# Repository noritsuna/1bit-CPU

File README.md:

# 1bit CPU made with ASIC (ISHI-Kai's OpenMPW PTC06-1)
[naoto64氏の1bit-CPU](https://naoto64.github.io/1bit-CPU/)を[ISHI会版OpenMPW PTC06-1](https://ishi-kai.org/openmpw/shuttle/ptc06/2024/07/06/shuttle_ISHI-Kai_OpenMPW-PTC06-1_start.html)を利用して、ASIC化しました！  
サイズは、280um x 65um くらいとなりました。元の基板が85mm x 70mmですのでおよそ36万分の1に縮小できました！  

# 論理回路化
まずは、74HC series logic IC部分を論理回路に起こし直して、シミュレーションを行いました。  
シミュレーションには[logicsim](http://www.cburch.com/logisim/)を利用しています。  

## 各種回路
本家のサンプル回路をシミュレーションしました。  

-[LED点滅回路](logicsim/LED_brink.circ)
 
-[LED点灯回路](logicsim/LED_flash.circ)
 
-[NOP回路](logicsim/NOP.circ)

# AISC化
ここから、ASICにするための設計を行なっていきます。  

## 回路図
まずは、回路図を書きます。とは言っても、シミュレーション時に回路としては完成しているので、それをxschemで書き直しただけです。  

-[回路図](xschem/1bit-CPU.sch)

## レイアウト
続いて、論理回路のレイアウトをします。  
論理回路は実際には、P-FETやN-FETを組み合わせて機能が実現されています。  

もちろん、P-FETやN-FETを組み合わせて、自分で論理回路のレイアウトをしても良いのですが、通常スタセル（スタンダードセル）という物が用意されています。  
要は、P-FETやN-FETを組み合わせて作られている論理回路ライブラリです。3つ目が拡大図でP-FETとN-FETで構成されているのが確認できるかと思います。  

回路図そのままで、スタセルを配置してみたパターンです。  

### 一列化
このまま配線するだけでも良いのですが、通常のスタセルはVerilogなどから自動的にレイアウトに変換する時に使用するように作成されています。  
そのため、スタセルは自動レイアウトを考慮して、下の図のように縦の長さが固定されて、上部にVDDがあり下部にVSS(GND)があるタイル状の形状をしています。これらを横に並べて利用することで、VSSやVSSが接続されて、自動ルーティングや配置がしやすいように作られています。  

そのため、人間が見やすい回路図の形で配置し、配線すると無駄が多くなります。  
そこで、回路図をこのタイル型レイアウトに合わせて、一列に並ぶように書き換えます。  
（通常は、この手の論理回路で設計するロジック回路を手でレイアウトすることはあまり無いと思いますので、今回は結構特殊なシチュエーションとなります。）  

-[1ライン化回路図](xschem/1bit-CPU_1line.sch)

### 最終レイアウト
一列化して、配線したレイアウトです。  

-[レイアウト](klayout/1bit-CPU.gds)

## LVS
手配線のため回路図とレイアウトが間違っている可能性があるため、LVS（Layout vs Schematic）をかけるのですが、OpenRule1umのスタセルの作りが微妙のため、完全体とはなりませんでした。  
そのため、目LVSで乗り切りました。とは言っても、接続先は下の図（LVSの配線ハイライト）のように強調表示されるためそれほど大変ではありません。  

## パッドへの接続
最後に、実際の半導体上のパッド（ピン）に各ポートを接続します。  
本来ならピンの設定（INやOUT、デジタルかアナログかなどを指定する）があるのですが、そこの設定はNDAの範囲内での設定となるため、ここでは行いません。そのため、これは実質的に仮配線となります。  

-[パッド付きレイアウト](klayout/1bit-CPU_frame.gds)

## WSL Image
上記の回路図やシミュレーション、レイアウト、DRC、LVSを実行するための環境をセットアップしたWSLイメージを用意しています。

- [WSL Image](https://www.noritsuna.jp/download/ubuntu2204_PTC06-1.tar.xz)
    - ID: ishikai
    - Pass: ishikai

### Installing WSL Images
`wsl --import-in-place ubuntu2204_PTC06-1 .\ubuntu2204_PTC06-1\ext4.vhdx`

起動には"ubuntu2204_PTC06-1.lnk"をご利用ください。  

### Deleting WSL Images
イメージも削除されるので注意してください。    

`wsl --unregister ubuntu2204_PTC06-1`

# [本チップ用ボード](kicad/1bit-CPU_board)
メモリや外部クロック、動作確認用のLEDを搭載したボードをKiCADで設計しました。  

[本チップ用ボードディレクトリ：KiCADファイル](kicad/1bit-CPU_board)

## 動作確認
ボードが到着したので、部品を実装して動作確認しました。  
無事に、本家の1bit-CPUボードと同じ動きをしております！  
※クロックが微妙にずれているため、同期はしてません。

[ボード：YouTube動画](https://youtube.com/shorts/-G9ZElhzAAo?feature=share)
[ボード：動画ファイル](images/1bit-CPU_board.mp4)

# [本チップ用ラズパイHAT](kicad/1bit-CPU_HAT)
ラズパイHATをKiCADで設計しました。  
ただ、本CPUは5V動作で、ラズパイは3.3V動作のため、レベル変換が必要となります。  

## インバータの応用
レベル変換の一つの手として、バッファ回路を使う手があります。  
バッファ回路＝インバータ回路*2です。そこで、今回は、みんなで実装したインバータ回路をそのまま使うことにしました。  

### インバータの動作確認
- [インバータ動作チェック用AD3設定ファイル](kicad/1bit-CPU_HAT/Inverter_checker.dwf3work)

## クロック源
クロック源として、りょうすさんが実装したVCOを流用しました。  

### クロック源の動作確認
- [VCO動作チェック用AD3設定ファイル](kicad/1bit-CPU_HAT/VCO_checker.dwf3work)

## HATの実装
チップ内にあるインバータ回路やVCOを利用したため、外部回路は3つのみとなっています。  

- LED点灯用回路
- リセット回路
- VCO用電圧制御回路

- [本チップ用ラズパイHATディレクトリ：KiCADファイル](kicad/1bit-CPU_HAT)

## 実行用インタープリター
ラズパイ用のプログラム実行用のインタープリターの実装です。

- [本CPU用インタープリター](kicad/1bit-CPU_HAT/program/1bit-CPU_interpreter.py)

## 実際のボード
実際にラズパイZEROに装着した状態と動作状態。

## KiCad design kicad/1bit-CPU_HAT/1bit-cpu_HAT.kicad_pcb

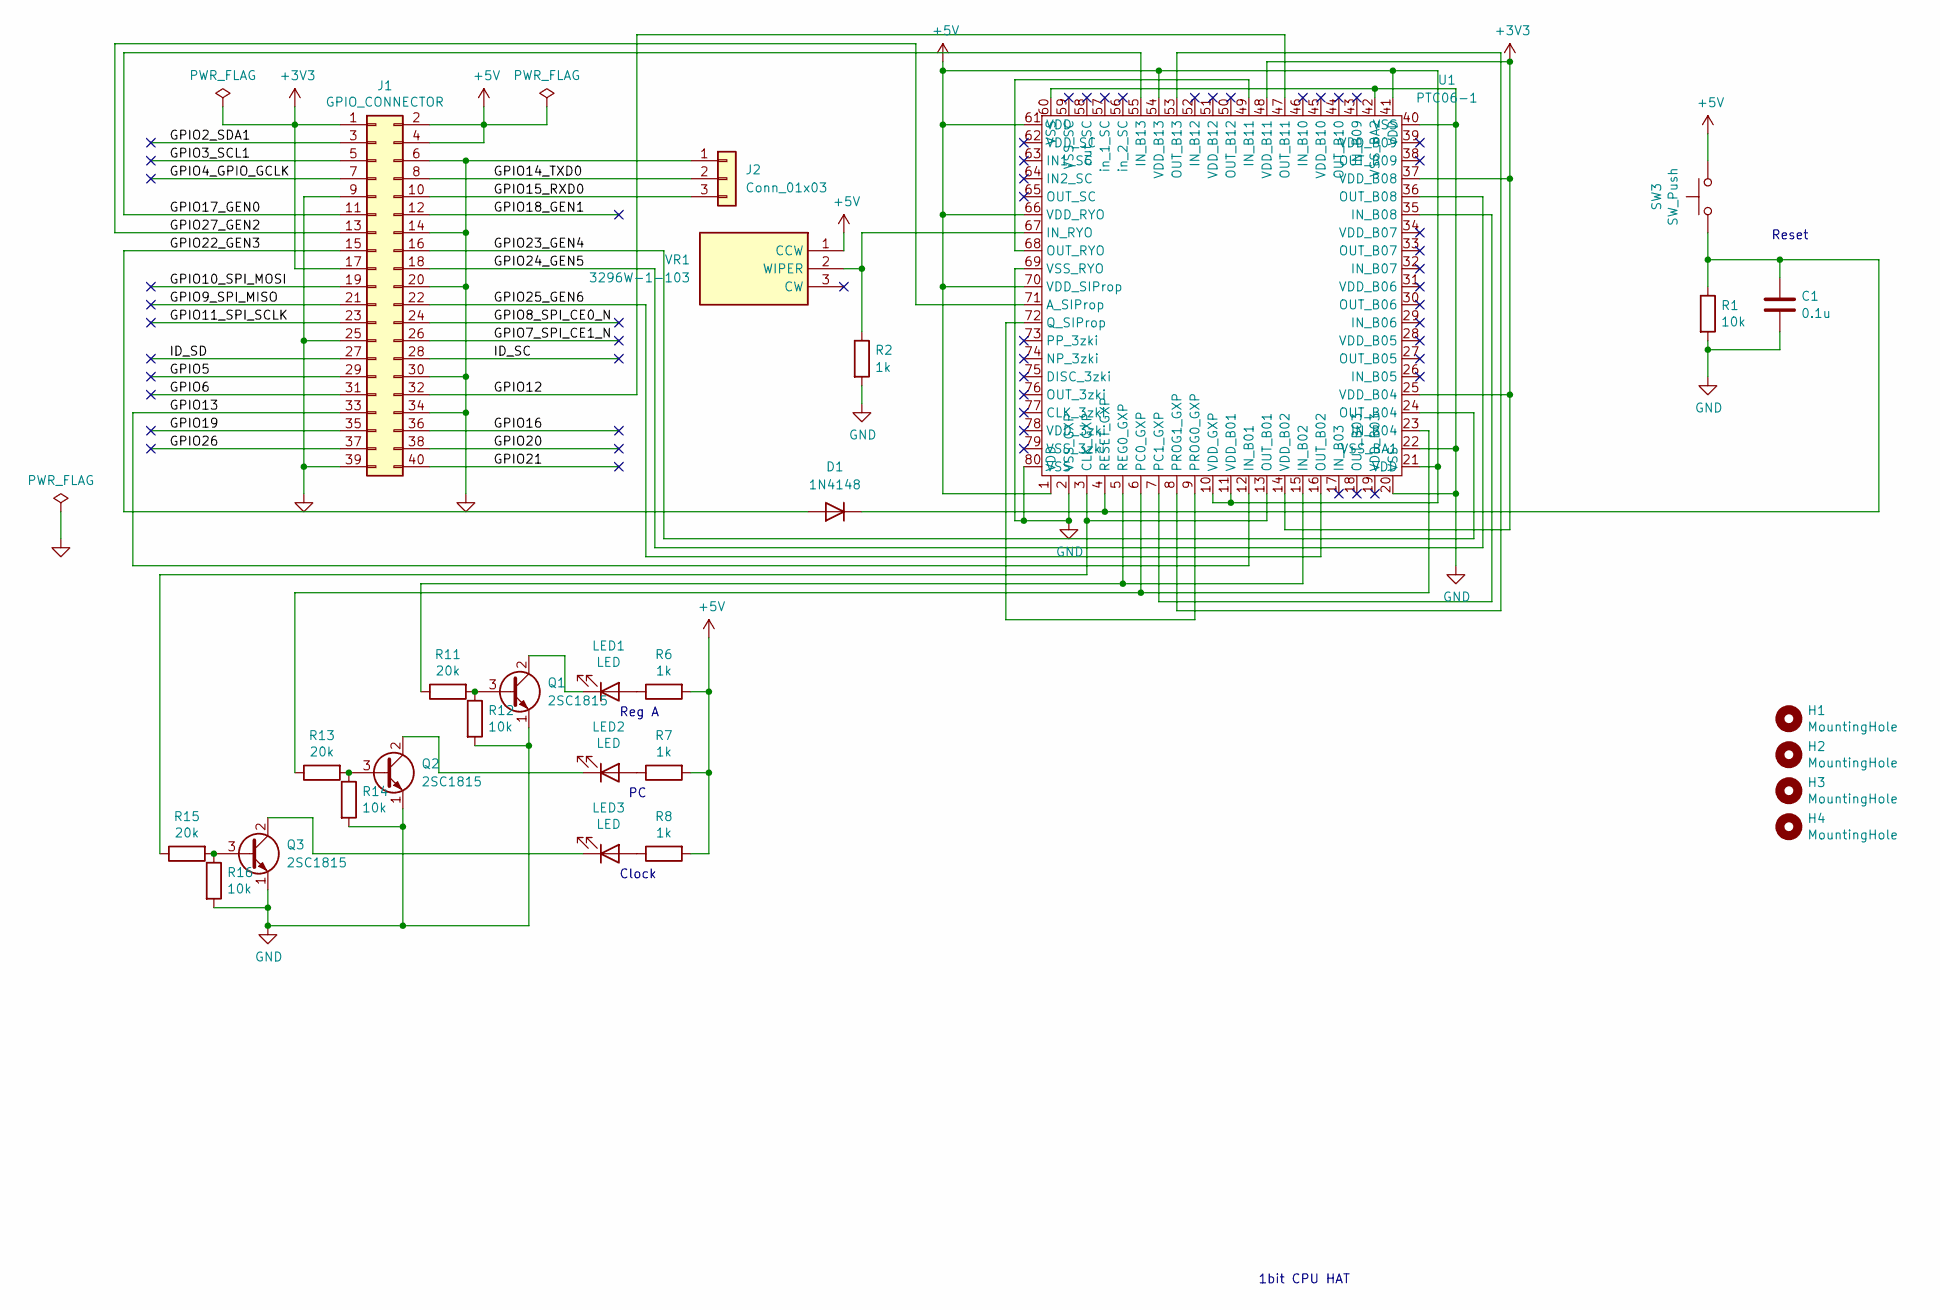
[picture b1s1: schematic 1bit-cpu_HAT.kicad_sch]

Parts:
C1: 0.1u; C_Disc_D4.3mm_W1.9mm_P5.00mm
D1: 1N4148; D_DO-35_SOD27_P7.62mm_Horizontal
H1, H2, H3, H4: MountingHole; MountingHole_2.7mm_M2.5_uHAT_RPi
J1: GPIO_CONNECTOR; PinSocket_2x20_P2.54mm_Vertical_Centered_Anchor
J2: Conn_01x03; PinHeader_1x03_P2.54mm_Vertical
LED1, LED2, LED3: LED; LED_D5.0mm
Q1, Q2, Q3: 2SC1815; TO-92_Inline
R1, R12, R14, R16: 10k; R_Axial_DIN0207_L6.3mm_D2.5mm_P7.62mm_Horizontal
R2, R6, R7, R8: 1k; R_Axial_DIN0207_L6.3mm_D2.5mm_P7.62mm_Horizontal
R11, R13, R15: 20k; R_Axial_DIN0207_L6.3mm_D2.5mm_P7.62mm_Horizontal
SW3: SW_Push; SW_PUSH_6mm
U1: PTC06-1; LQFP-80_12x12mm_P0.5mm
VR1: 3296W-1-103; 3296W1103; Mouser Part Number 652-3296W-1-103

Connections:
+3V3: J1.1, J1.17, U1.14 (VDD_B02), U1.25 (VDD_B04), U1.37 (VDD_B08), U1.48 (VDD_B11)
+5V: J1.2, J1.4, R6.2, R7.2, R8.2, SW3.1, U1.1 (VDD), U1.10 (VDD_GXP), U1.11 (VDD_B01), U1.21 (VDD), U1.41 (VDD), U1.54 (VDD_B13), U1.61 (VDD), U1.66 (VDD_RYO), U1.70 (VDD_SIProp), VR1.1 (CCW)
/GPIO2_SDA1: J1.3
/GPIO3_SCL1: J1.5
/GPIO4_GPIO_GCLK: J1.7
/GPIO5: J1.29
/GPIO6: J1.31
/GPIO7_SPI_CE1_N: J1.26
/GPIO8_SPI_CE0_N: J1.24
/GPIO9_SPI_MISO: J1.21
/GPIO10_SPI_MOSI: J1.19
/GPIO11_SPI_SCLK: J1.23
/GPIO12: J1.32, U1.47 (OUT_B11)
/GPIO13: J1.33, U1.12 (IN_B01)
/GPIO14_TXD0: J1.8, J2.2
/GPIO15_RXD0: J1.10, J2.3
/GPIO16: J1.36
/GPIO17_GEN0: J1.11, U1.55 (IN_B13)
/GPIO18_GEN1: J1.12
/GPIO19: J1.35
/GPIO20: J1.38
/GPIO21: J1.40
/GPIO22_GEN3: D1.2 (A), J1.15
/GPIO23_GEN4: J1.16, U1.24 (OUT_B04)
/GPIO24_GEN5: J1.18, U1.36 (OUT_B08)
/GPIO25_GEN6: J1.22, U1.16 (OUT_B02)
/GPIO26: J1.37
/GPIO27_GEN2: J1.13, U1.71 (A_SIProp)
/ID_SC: J1.28
/ID_SD: J1.27
GND: C1.1, J1.6, J1.9, J1.14, J1.20, J1.25, J1.30, J1.34, J1.39, J2.1, Q1.1 (E), Q2.1 (E), Q3.1 (E), R1.2, R2.2, R12.2, R14.2, R16.2, U1.2 (VSS_GXP), U1.20 (VSS), U1.22 (VSS_BA1), U1.40 (VSS), U1.42 (VSS_BA2), U1.60 (VSS), U1.69 (VSS_RYO), U1.80 (VSS)
unnamed: C1.2, D1.1 (K), R1.1, SW3.2, U1.4 (RESET_GXP)
unnamed: LED1.2 (A), R6.1
unnamed: LED1.1 (K), Q1.2 (C)
unnamed: LED2.2 (A), R7.1
unnamed: LED2.1 (K), Q2.2 (C)
unnamed: LED3.2 (A), R8.1
unnamed: LED3.1 (K), Q3.2 (C)
unnamed: Q1.3 (B), R11.2, R12.1
unnamed: Q2.3 (B), R13.2, R14.1
unnamed: Q3.3 (B), R15.2, R16.1
unnamed: R15.1, U1.3 (CLK_GXP), U1.13 (OUT_B01)
unnamed: R11.1, U1.5 (REG0_GXP), U1.15 (IN_B02)
unnamed: R13.1, U1.6 (PC0_GXP), U1.23 (IN_B04)
unnamed: U1.7 (PC1_GXP), U1.35 (IN_B08)
unnamed: U1.49 (IN_B11), U1.68 (OUT_RYO)
unnamed: R2.1, U1.67 (IN_RYO), VR1.2 (WIPER)
unnamed: U1.8 (PROG1_GXP), U1.53 (OUT_B13)
unnamed: U1.9 (PROG0_GXP), U1.72 (Q_SIProp)

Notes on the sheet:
Reg A
1bit CPU HAT
Clock
Reset

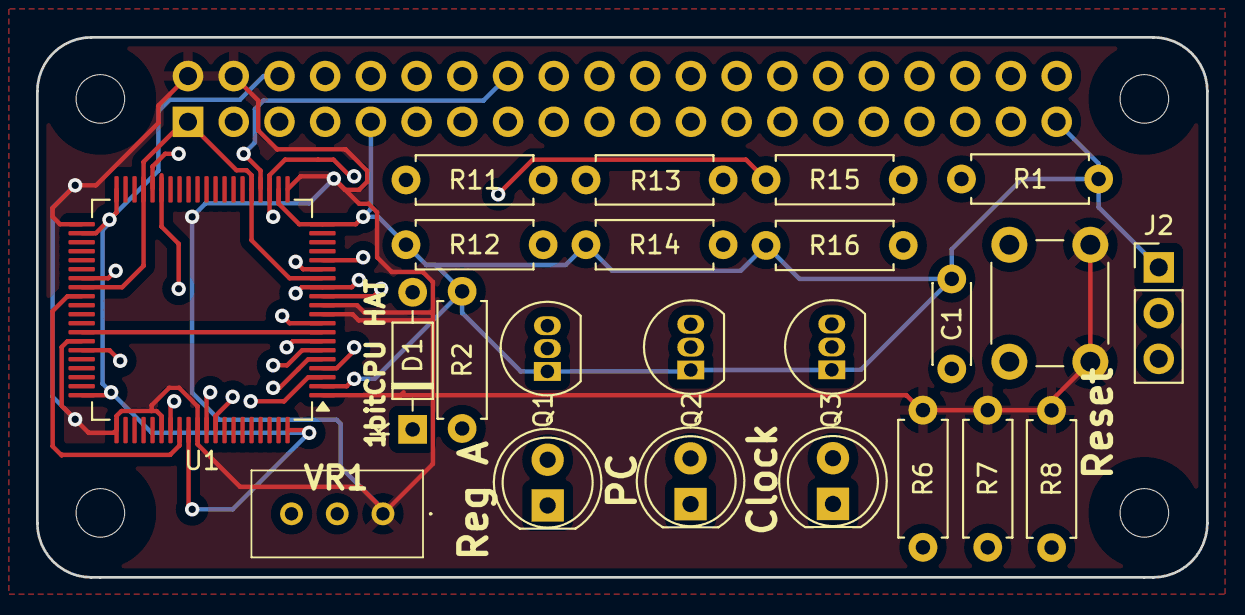
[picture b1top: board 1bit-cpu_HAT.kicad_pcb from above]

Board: 4 copper layers, 65.0 x 30.0 mm, 28 parts (1 on the bottom side), 31 nets.

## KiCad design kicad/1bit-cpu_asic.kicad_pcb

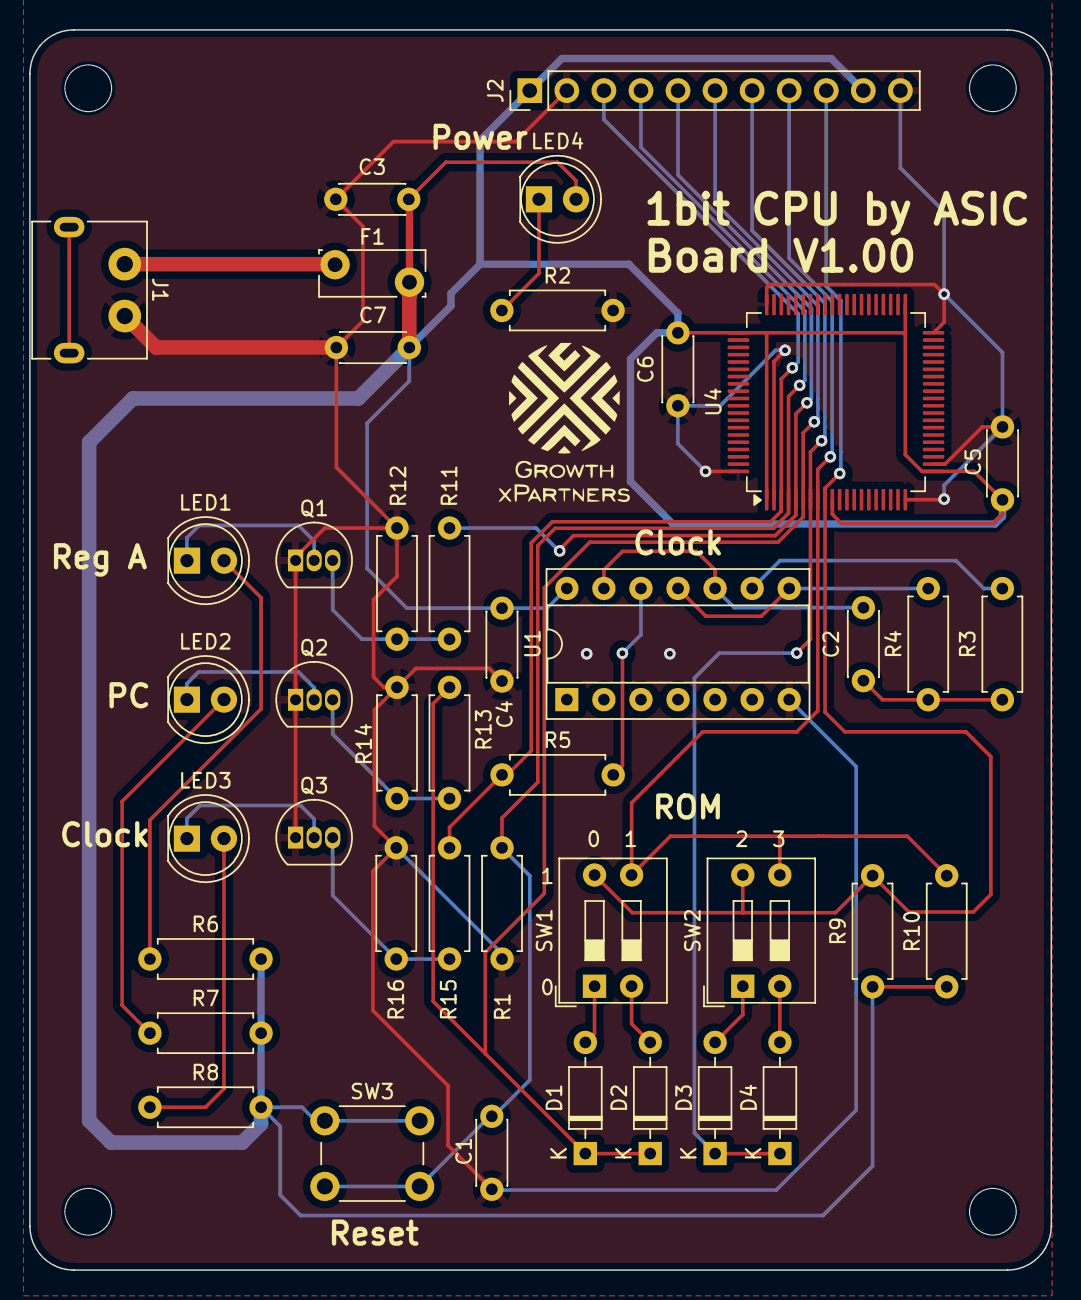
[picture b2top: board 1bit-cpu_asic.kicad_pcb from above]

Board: 2 copper layers, 70.0 x 85.0 mm, 46 parts (0 on the bottom side), 29 nets.

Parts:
C1, C4, C5, C6, C7: 0.1u; C_Disc_D4.3mm_W1.9mm_P5.00mm
C2, C3: 10u; C_Disc_D4.3mm_W1.9mm_P5.00mm
D1, D2, D3, D4: 1N4148; D_DO-35_SOD27_P7.62mm_Horizontal
F1: 100mA; Fuse_Bourns_MF-RG300
H1, H2, H3, H4: MountingHole; MountingHole_3.2mm_M3
J1: USB_C_Receptacle_PowerOnly_6P; USB_C_PowerOnly
J2: Conn_01x11; PinHeader_1x11_P2.54mm_Vertical
LED1, LED2, LED3, LED4: LED; LED_D5.0mm
Q1, Q2, Q3: 2SC1815; TO-92_Inline
R1, R5, R9, R10, R12, R14, R16: 10k; R_Axial_DIN0207_L6.3mm_D2.5mm_P7.62mm_Horizontal
R2, R6, R7, R8: 1k; R_Axial_DIN0207_L6.3mm_D2.5mm_P7.62mm_Horizontal
R3: 100k; R_Axial_DIN0207_L6.3mm_D2.5mm_P7.62mm_Horizontal
R4: 47k; R_Axial_DIN0207_L6.3mm_D2.5mm_P7.62mm_Horizontal
R11, R13, R15: 20k; R_Axial_DIN0207_L6.3mm_D2.5mm_P7.62mm_Horizontal
SW1, SW2: SW; SW_DIP_SPSTx02_Slide_9.78x7.26mm_W7.62mm_P2.54mm
SW3: SW_Push; SW_PUSH_6mm
U1: 74HC04; DIP-14_W7.62mm_Socket
U4: PTC06-1; LQFP-80_12x12mm_P0.5mm

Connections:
+5V: C3.2, C4.2, C5.2, C6.2, C7.2, F1.2, J2.1, J2.10, LED4.2 (A), R6.2, R7.2, R8.2, R9.1, R10.1, SW3.1, U1.14 (VCC), U4.1 (VDD), U4.10 (VDD_GXP), U4.21 (VDD), U4.41 (VDD), U4.61 (VDD)
GND: C1.1, C3.1, C4.1, C5.1, C6.1, C7.1, J1.A12 (GND), J2.2, J2.11, Q1.1 (E), Q2.1 (E), Q3.1 (E), R1.2, R2.2, R12.2, R14.2, R16.2, U1.7 (GND), U4.2 (VSS_GXP), U4.20 (VSS), U4.22 (VSS_BA1), U4.40 (VSS), U4.42 (VSS_BA2), U4.60 (VSS), U4.80 (VSS)
unnamed: C2.1, R3.1, R4.1
unnamed: C2.2, U1.10, U1.13
unnamed: D1.2 (A), SW1.1
unnamed: D1.1 (K), D2.1 (K), J2.6, R13.1, U4.6 (PC0_GXP)
unnamed: D2.2 (A), SW1.2
unnamed: D3.2 (A), SW2.1
unnamed: D3.1 (K), D4.1 (K), J2.7, U4.7 (PC1_GXP)
unnamed: D4.2 (A), SW2.2
unnamed: F1.1, J1.A9 (VBUS)
unnamed: J2.3, R5.1, R15.1, U4.3 (CLK_GXP)
unnamed: C1.2, J2.4, R1.1, SW3.2, U4.4 (RESET_GXP)
unnamed: J2.5, R11.1, U4.5 (REG0_GXP)
unnamed: J2.8, R10.2, SW1.3, SW2.3, U4.8 (PROG1_GXP)
unnamed: J2.9, R9.2, SW1.4, SW2.4, U4.9 (PROG0_GXP)
unnamed: LED1.2 (A), R6.1
unnamed: LED1.1 (K), Q1.2 (C)
unnamed: LED2.2 (A), R7.1
unnamed: LED2.1 (K), Q2.2 (C)
unnamed: LED3.2 (A), R8.1
unnamed: LED3.1 (K), Q3.2 (C)
unnamed: LED4.1 (K), R2.1
unnamed: Q1.3 (B), R11.2, R12.1
unnamed: Q2.3 (B), R13.2, R14.1
unnamed: Q3.3 (B), R15.2, R16.1
unnamed: R3.2, U1.9
unnamed: R4.2, U1.8, U1.11
unnamed: R5.2, U1.12

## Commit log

2024-07-20 Add 1st commit.
    Add 1st commit.
2024-07-20 Fix typo.
    Fix typo.
2024-07-21 Change Pin's VIA.
    Change Pin's VIA.
2024-07-21 Fix schematic.
    Fix schematic.
2024-07-25 Fix LVS model.
    Fix LVS model.
2024-07-25 Fix schemtic.
    Fix schemtic.
2024-07-26 Change port VIA.
    Change port VIA.
2024-07-28 Add frame.
    Add frame.
2024-07-29 Replace New Pad.
    Replace New Pad.
2025-01-28 Add KiCAD data.
    Add KiCAD data.
2025-02-11 Fix U4's 20&21 pin.
    Fix U4's 20&21 pin.
2025-02-11 Fix U4's 40&41 pins.
    Fix U4's 40&41 pins.
2025-02-11 Add board movie.
    Add board movie.
2025-02-28 Add 1bit-CPU HAT.
    Add 1bit-CPU HAT.
2025-03-04 Add Real HAT board.
    Add Real HAT board.
2025-12-09 Add WSL Image.
    Add WSL Image.
